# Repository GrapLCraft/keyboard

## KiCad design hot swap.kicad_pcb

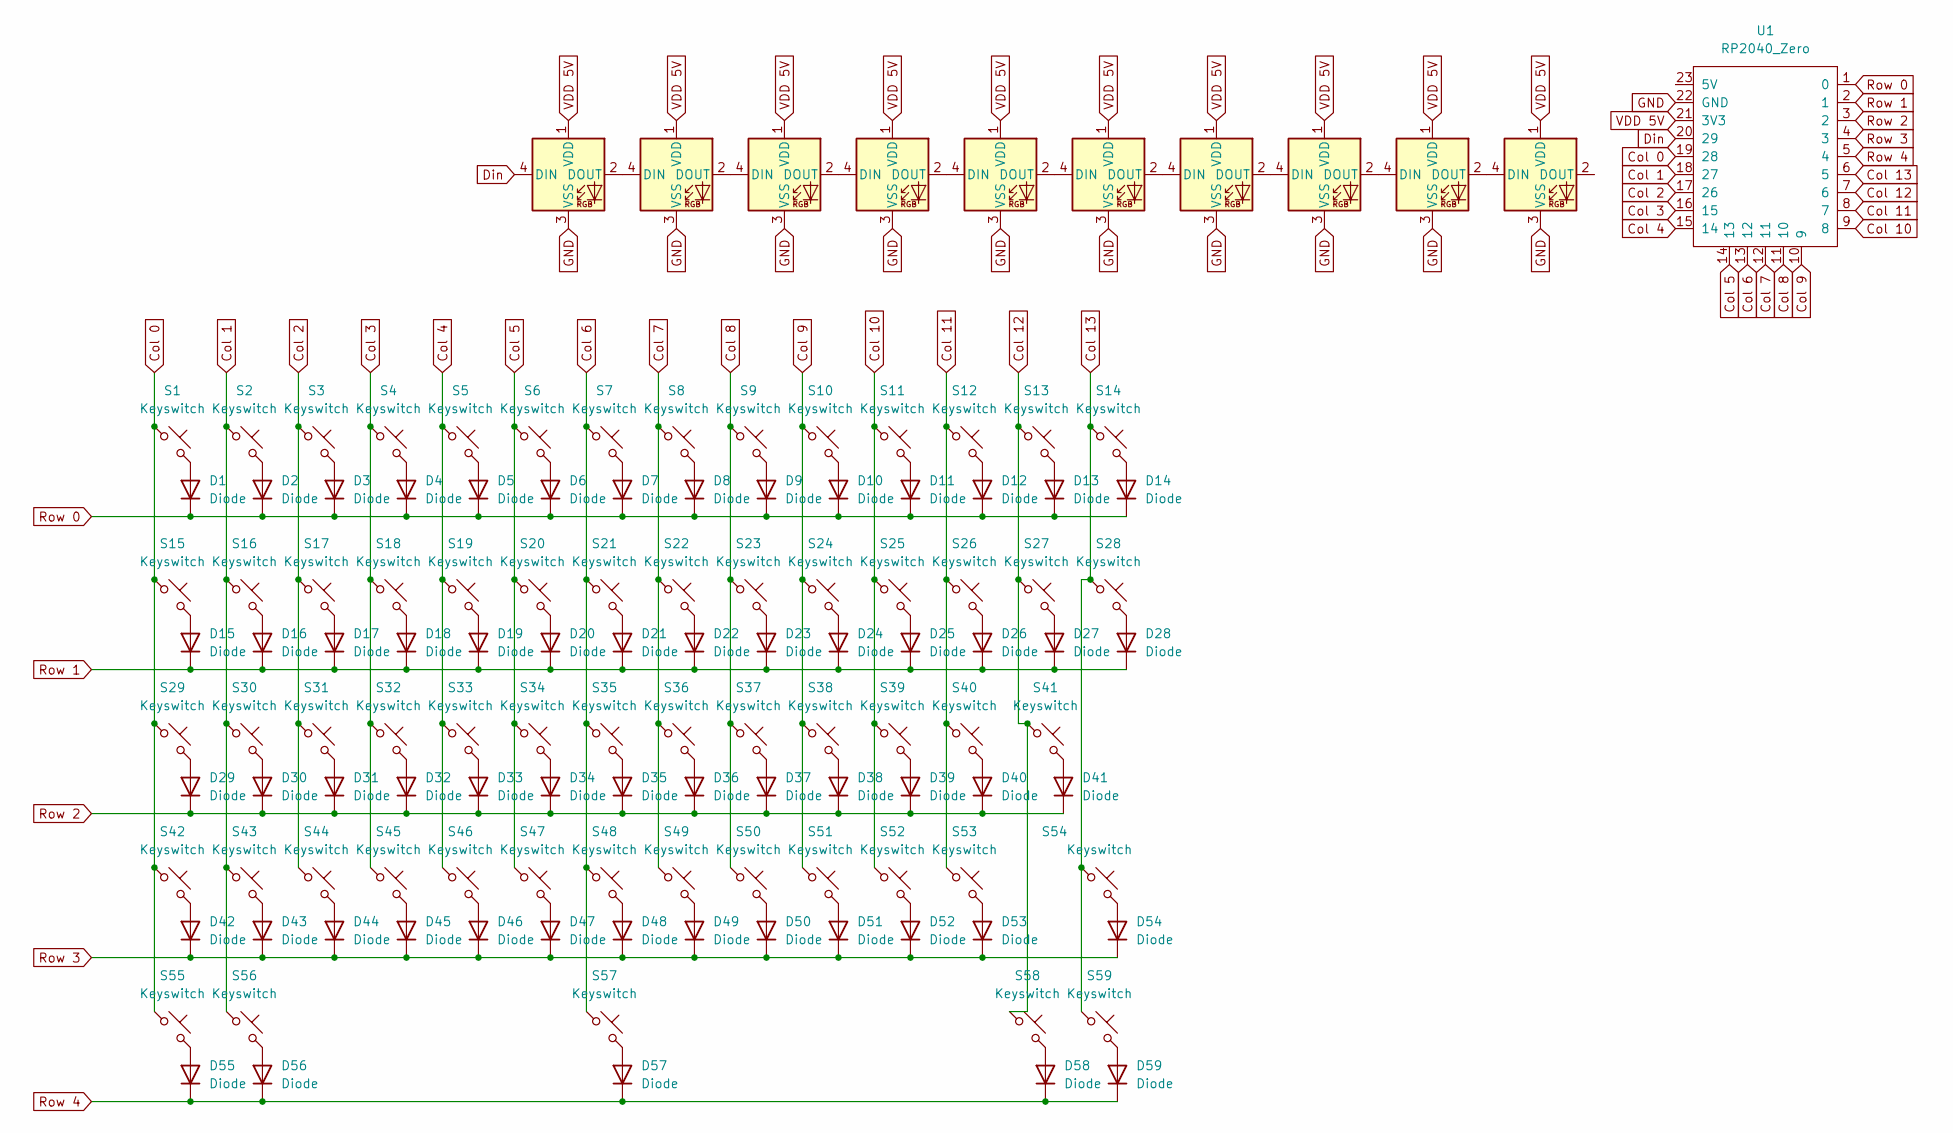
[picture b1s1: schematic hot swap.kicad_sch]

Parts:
D1, D2, D3, D4, D5, D6, D7, D8, D9, D10, D11, D12, D13, D14, D15, D16, D17, D18, D19, D20, D21, D22, D23, D24, D25, D26, D27, D28, D29, D30, D31, D32, D33, D34, D35, D36, D37, D38, D39, D40, D41, D42, D43, D44, D45, D46, D47, D48, D49, D50, D51, D52, D53, D54, D55, D56, D57, D58, D59: Diode; Diode_DO-35
D60, D61, D62, D63, D64, D65, D66, D67, D68, D69: LED_WS2812B
S1, S2, S3, S4, S5, S6, S7, S8, S9, S10, S11, S12, S13, S16, S17, S18, S19, S20, S21, S22, S23, S24, S25, S26, S27, S30, S31, S32, S33, S34, S35, S36, S37, S38, S39, S40, S43, S44, S45, S46, S47, S48, S49, S50, S51, S52, S54, S55, S59: Keyswitch; MX_PCB_1.00u
S14: Keyswitch; MX_PCB_2.00u
S15, S28, S56, S58: Keyswitch; MX_PCB_1.50u
S29, S53: Keyswitch; MX_PCB_1.75u
S41, S42: Keyswitch; MX_PCB_2.25u
S57: Keyswitch; MX_PCB_7.00u
U1: RP2040_Zero

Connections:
Col 0: S1.1, S15.1, S29.1, S42.1, S55.1, U1.19 (28)
Col 1: S2.1, S16.1, S30.1, S43.1, S56.1, U1.18 (27)
Col 2: S3.1, S17.1, S31.1, S44.1, U1.17 (26)
Col 3: S4.1, S18.1, S32.1, S45.1, U1.16 (15)
Col 4: S5.1, S19.1, S33.1, S46.1, U1.15 (14)
Col 5: S6.1, S20.1, S34.1, S47.1, U1.14 (13)
Col 6: S7.1, S21.1, S35.1, S48.1, S57.1, U1.13 (12)
Col 7: S8.1, S22.1, S36.1, S49.1, U1.12 (11)
Col 8: S9.1, S23.1, S37.1, S50.1, U1.11 (10)
Col 9: S10.1, S24.1, S38.1, S51.1, U1.10 (9)
Col 10: S11.1, S25.1, S39.1, S52.1, U1.9 (8)
Col 11: S12.1, S26.1, S40.1, S53.1, U1.8 (7)
Col 12: S13.1, S27.1, S41.1, S58.1, U1.7 (6)
Col 13: S14.1, S28.1, S54.1, S59.1, U1.6 (5)
Din: D60.4 (DIN), U1.20 (29)
GND: D60.3 (VSS), D61.3 (VSS), D62.3 (VSS), D63.3 (VSS), D64.3 (VSS), D65.3 (VSS), D66.3 (VSS), D67.3 (VSS), D68.3 (VSS), D69.3 (VSS), U1.22 (GND)
unnamed: D1.2 (A), S1.2
unnamed: D2.2 (A), S2.2
unnamed: D3.2 (A), S3.2
unnamed: D4.2 (A), S4.2
unnamed: D5.2 (A), S5.2
unnamed: D6.2 (A), S6.2
unnamed: D7.2 (A), S7.2
unnamed: D8.2 (A), S8.2
unnamed: D9.2 (A), S9.2
unnamed: D10.2 (A), S10.2
unnamed: D11.2 (A), S11.2
unnamed: D12.2 (A), S12.2
unnamed: D13.2 (A), S13.2
unnamed: D14.2 (A), S14.2
unnamed: D15.2 (A), S15.2
unnamed: D16.2 (A), S16.2
unnamed: D17.2 (A), S17.2
unnamed: D18.2 (A), S18.2
unnamed: D19.2 (A), S19.2
unnamed: D20.2 (A), S20.2
unnamed: D21.2 (A), S21.2
unnamed: D22.2 (A), S22.2
unnamed: D23.2 (A), S23.2
unnamed: D24.2 (A), S24.2
unnamed: D25.2 (A), S25.2
unnamed: D26.2 (A), S26.2
unnamed: D27.2 (A), S27.2
unnamed: D28.2 (A), S28.2
unnamed: D29.2 (A), S29.2
unnamed: D30.2 (A), S30.2
unnamed: D31.2 (A), S31.2
unnamed: D32.2 (A), S32.2
unnamed: D33.2 (A), S33.2
unnamed: D34.2 (A), S34.2
unnamed: D35.2 (A), S35.2
unnamed: D36.2 (A), S36.2
unnamed: D37.2 (A), S37.2
unnamed: D38.2 (A), S38.2
unnamed: D39.2 (A), S39.2
unnamed: D40.2 (A), S40.2
unnamed: D41.2 (A), S41.2
unnamed: D42.2 (A), S42.2
unnamed: D43.2 (A), S43.2
unnamed: D44.2 (A), S44.2
unnamed: D45.2 (A), S45.2
unnamed: D46.2 (A), S46.2
unnamed: D47.2 (A), S47.2
unnamed: D48.2 (A), S48.2
unnamed: D49.2 (A), S49.2
unnamed: D50.2 (A), S50.2
unnamed: D51.2 (A), S51.2
unnamed: D52.2 (A), S52.2
unnamed: D53.2 (A), S53.2
unnamed: D54.2 (A), S54.2
unnamed: D55.2 (A), S55.2
unnamed: D56.2 (A), S56.2
unnamed: D57.2 (A), S57.2
unnamed: D58.2 (A), S58.2
unnamed: D59.2 (A), S59.2
unnamed: D60.2 (DOUT), D61.4 (DIN)
unnamed: D61.2 (DOUT), D62.4 (DIN)
unnamed: D62.2 (DOUT), D63.4 (DIN)
unnamed: D63.2 (DOUT), D64.4 (DIN)
unnamed: D64.2 (DOUT), D65.4 (DIN)
unnamed: D65.2 (DOUT), D66.4 (DIN)
unnamed: D66.2 (DOUT), D67.4 (DIN)
unnamed: D67.2 (DOUT), D68.4 (DIN)
unnamed: D68.2 (DOUT), D69.4 (DIN)
Row 0: D1.1 (K), D2.1 (K), D3.1 (K), D4.1 (K), D5.1 (K), D6.1 (K), D7.1 (K), D8.1 (K), D9.1 (K), D10.1 (K), D11.1 (K), D12.1 (K), D13.1 (K), D14.1 (K), U1.1 (0)
Row 1: D15.1 (K), D16.1 (K), D17.1 (K), D18.1 (K), D19.1 (K), D20.1 (K), D21.1 (K), D22.1 (K), D23.1 (K), D24.1 (K), D25.1 (K), D26.1 (K), D27.1 (K), D28.1 (K), U1.2 (1)
Row 2: D29.1 (K), D30.1 (K), D31.1 (K), D32.1 (K), D33.1 (K), D34.1 (K), D35.1 (K), D36.1 (K), D37.1 (K), D38.1 (K), D39.1 (K), D40.1 (K), D41.1 (K), U1.3 (2)
Row 3: D42.1 (K), D43.1 (K), D44.1 (K), D45.1 (K), D46.1 (K), D47.1 (K), D48.1 (K), D49.1 (K), D50.1 (K), D51.1 (K), D52.1 (K), D53.1 (K), D54.1 (K), U1.4 (3)
Row 4: D55.1 (K), D56.1 (K), D57.1 (K), D58.1 (K), D59.1 (K), U1.5 (4)
VDD 5V: D60.1 (VDD), D61.1 (VDD), D62.1 (VDD), D63.1 (VDD), D64.1 (VDD), D65.1 (VDD), D66.1 (VDD), D67.1 (VDD), D68.1 (VDD), D69.1 (VDD), U1.21 (3V3)

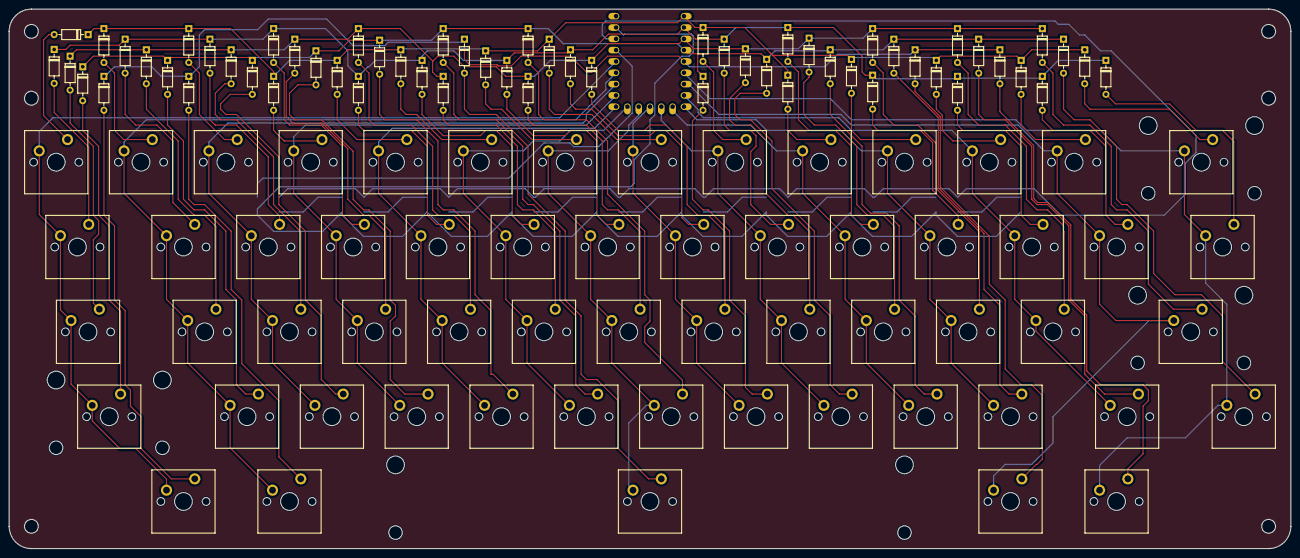
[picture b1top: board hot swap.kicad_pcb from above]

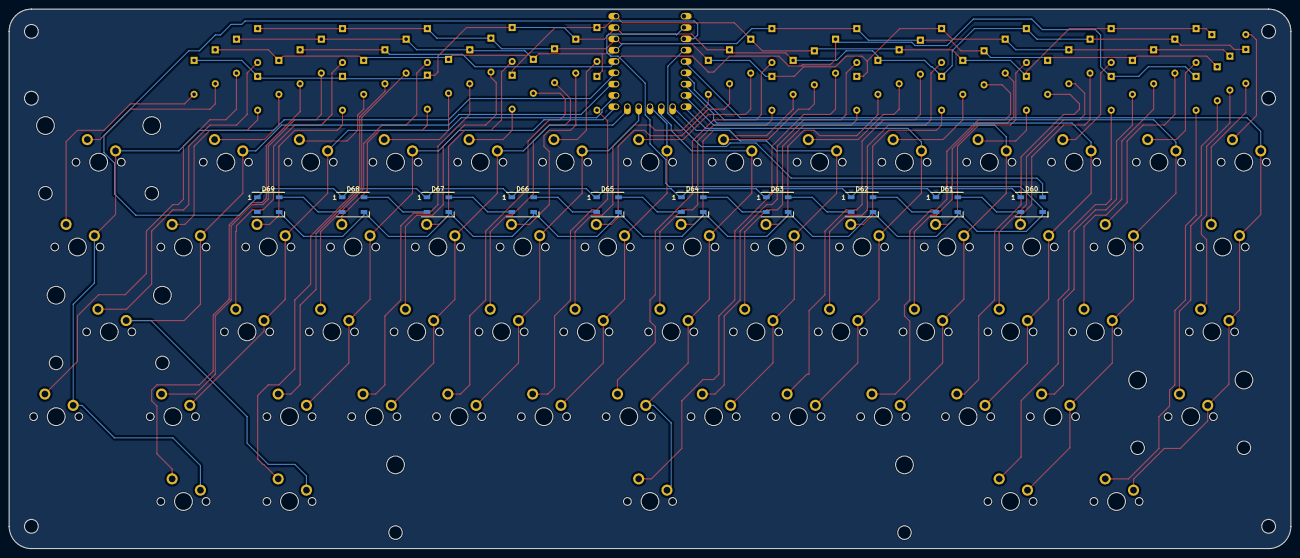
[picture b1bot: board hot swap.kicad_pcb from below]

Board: 2 copper layers, 287.9 x 121.1 mm, 129 parts (10 on the bottom side), 90 nets.

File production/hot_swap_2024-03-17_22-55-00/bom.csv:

Designator,Footprint,Quantity,Value,LCSC Part #
"D1, D10, D11, D12, D13, D14, D15, D16, D17, D18, D19, D2, D20, D21, D22, D23, D24, D25, D26, D27, D28, D29, D3, D30, D31, D32, D33, D34, D35, D36, D37, D38, D39, D4, D40, D41, D42, D43, D44, D45, D46, D47, D48, D49, D5, D50, D51, D52, D53, D54, D55, D56, D57, D58, D59, D6, D7, D8, D9",Diode_DO-35,59,Diode,
"D60, D61, D62, D63, D64, D65, D66, D67, D68, D69",LED_WS2812B,10,LED_WS2812B,
"S1, S10, S11, S12, S13, S16, S17, S18, S19, S2, S20, S21, S22, S23, S24, S25, S26, S27, S3, S30, S31, S32, S33, S34, S35, S36, S37, S38, S39, S4, S40, S43, S44, S45, S46, S47, S48, S49, S5, S50, S51, S52, S54, S55, S59, S6, S7, S8, S9",MX_PCB_1.00u,49,Keyswitch,
S14,MX_PCB_2.00u,1,Keyswitch,
"S15, S28, S56, S58",MX_PCB_1.50u,4,Keyswitch,
"S29, S53",MX_PCB_1.75u,2,Keyswitch,
"S41, S42",MX_PCB_2.25u,2,Keyswitch,
S57,MX_PCB_7.00u,1,Keyswitch,
U1,RP2040_Zero,1,RP2040_Zero,
